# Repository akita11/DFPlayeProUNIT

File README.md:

# DFPlayerProUNIT

DFRobotの音声プレーヤモジュール[DFPlayer Pro](https://www.switch-science.com/products/8005)をGrove端子を接続して制御できるモジュールです。Grove端子からシリアル(UART)通信で音声再生などを制御することができます。（UIFlow(v1)用のブロックも用意する予定）

※DFPlayerProは付属していません

## 使い方（接続方法）

以下のようにスピーカやアンプを接続し、Grove端子からの制御で音声を再生します。また基板上の"PAYE"と"KEY"のシルクが示されている2組の端子は、それぞれDFPlayerProのKEY、PLAY端子に接続されていますので、これらを使って再生を制御することもできます（詳細はDFPlayerProのマニュアルを参照してください）

### アンプ付きスピーカに接続する場合

3.5mmジャック（ステレオ：上部中央）に3.5mmステレオケーブル等でアンプに接続します。

### スピーカを直接接続する場合

本体上部の2つの2.54mmた端子にスピーカを接続します。spkLとspkRがそれぞれお左と右のスピーカです。基板中央部に1.25mmピッチコネクタ(Molex 53047-0210用)をとりつける端子があり、市販の小型スピーカ（M5Stack本体に使われているものなど。AliExpressやTaobaoでも同等品があります）を接続することができます。

### 3.5mmジャックに直接スピーカを接続する方法

3.5mmジャックに直接スピーカを接続することもできます。その場合は、基板裏面のハンダジャンパを以下のように修正してください。

- JP1をカット
- JP2・JP3の中央と△マーク側をカットし、中央と反対側（△マークがない側）をショート

## 使い方（ソフトウエア）

あらかじめ、DFPlayerProをUSB Type-Cケーブルを使ってPCへ接続し、現れるドライブに使用する音声データ（*.mp3等）をコピーしておきます。（このときコピーした順番が、再生時に使用する「曲番号」になります）

### UIFlow(v1)での使い方

「DFPlayerPro.m5b」をダウンロードし、UIFlow(v1)の"Custom"の"Open *.m5b"からこのファイルを指定すると、Init、Play、Volumeの3つのブロックを使用できます。

- DFPlayerPro_Init : 初期化。最初に1回だけ読み出します。"TX"と"RX"には、使用するGroveポート・マイコン本体にあわせて、使用するピン番号を指定します。例えば、M5StackBasicのPortA（本体の赤いコネクタ）の場合は、上図のようにTX=21、RX=22を指定します。M5StackCore2のPortAの場合は、TX=32、RX=33となります。
- DFPlayerPro_Play : numに指定した「曲番号」の音声を再生します。
- DFPlayerPro_Volume : volに指定した音量に設定します。

### その他のソフトウエアでの使い方

Arduino用にはライブラリがあるようなので、そちらを使ってもOKです。
あるいは、DFPlayerProのデータシート等を参考に、制御コマンドを送信して使用してください。

## Author

Junichi Akita (@akita11) / akita@ifdl.jp

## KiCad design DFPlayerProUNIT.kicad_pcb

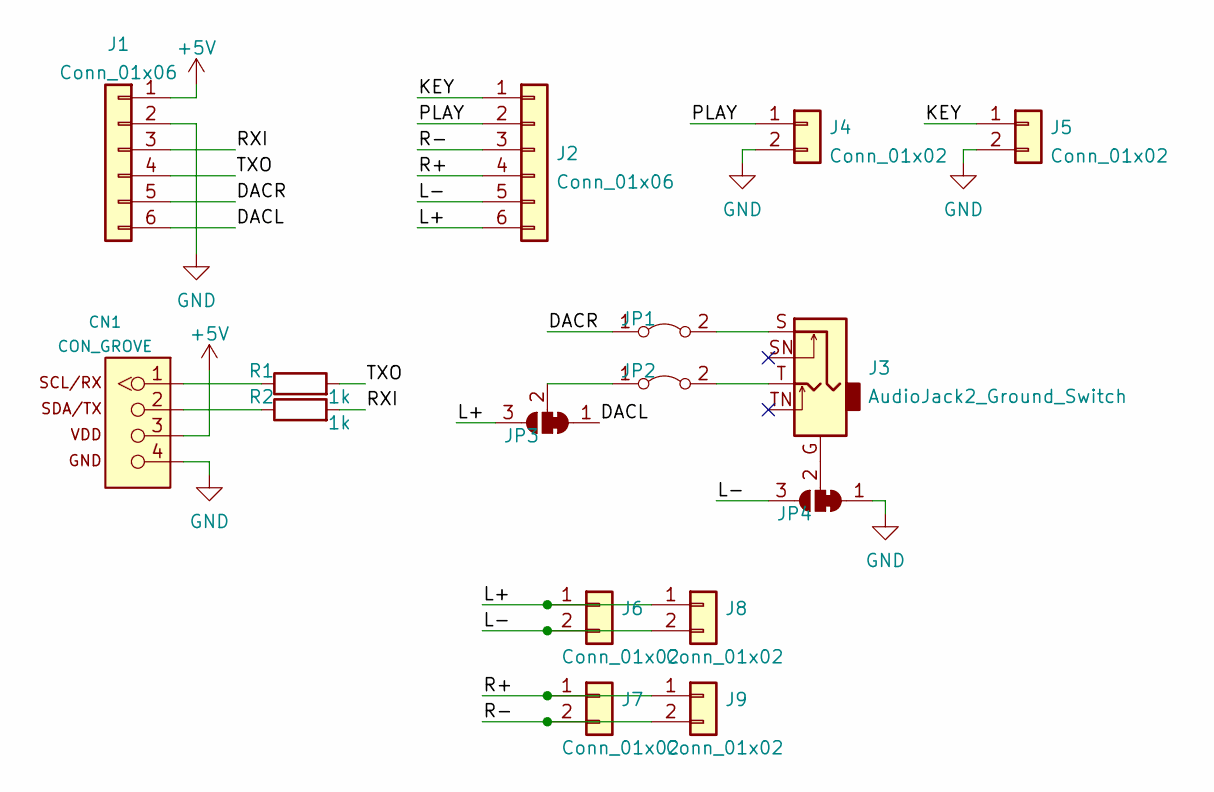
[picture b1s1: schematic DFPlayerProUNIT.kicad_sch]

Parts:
CN1: CON_GROVE; CON_GROVE_H
J1, J2: Conn_01x06; PinSocket_1x06_P2.54mm_Vertical
J3: AudioJack2_Ground_Switch; CON_AJ-1780
J4, J5, J6, J7: Conn_01x02; PinSocket_1x02_P2.54mm_Vertical
J8, J9: Conn_01x02; Molex_PicoBlade_53047-0210_1x02_P1.25mm_Vertical
JP1, JP2: Jumper_2_Bridged; SolderJumper-2_P1.3mm_Bridged2Bar_Pad1.0x1.5mm
JP3, JP4: SolderJumper_3_Bridged12; SolderJumper-3_P1.3mm_Bridged12_Pad1.0x1.5mm
R1, R2: 1k; R_0603_1608Metric

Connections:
+5V: CN1.3, J1.1
/DACL: J1.6, JP3.1 (A)
/DACR: J1.5, JP1.1 (A)
/KEY: J2.1, J5.1
/L+: J2.6, J6.1, J8.1, JP3.3 (B)
/L-: J2.5, J6.2, J8.2, JP4.3 (B)
/PLAY: J2.2, J4.1
/R+: J2.4, J7.1, J9.1
/R-: J2.3, J7.2, J9.2
/RXI: J1.3, R2.2
/TXO: J1.4, R1.2
GND: CN1.4, J1.2, J4.2, J5.2, JP4.1 (A)
unnamed: CN1.1, R1.1
unnamed: CN1.2, R2.1
unnamed: J3.S, JP1.2 (B)
unnamed: J3.T, JP2.2 (B)
unnamed: JP2.1 (A), JP3.2 (C)
unnamed: J3.G, JP4.2 (C)

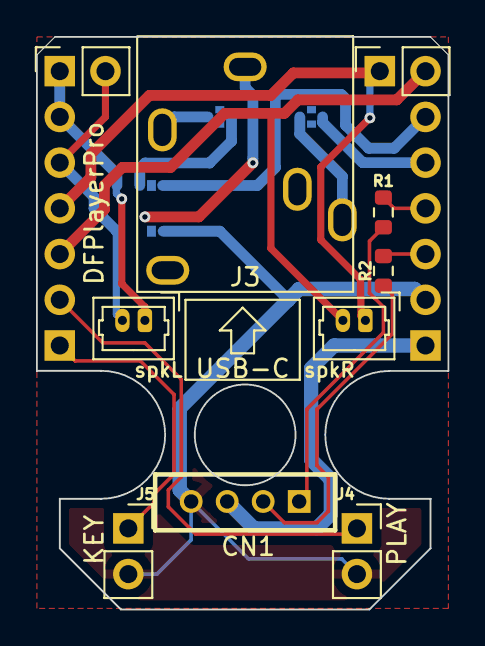
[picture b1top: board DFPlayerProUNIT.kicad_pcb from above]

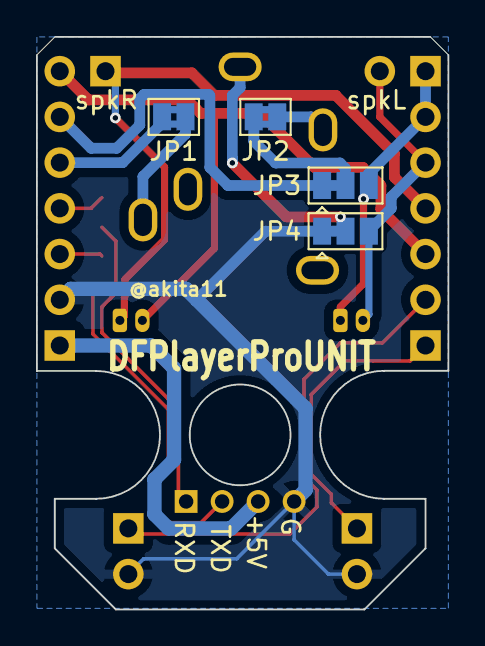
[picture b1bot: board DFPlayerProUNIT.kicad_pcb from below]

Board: 2 copper layers, 22.9 x 31.8 mm, 16 parts (4 on the bottom side), 18 nets.

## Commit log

2025-01-02 add photo
2025-01-02 typo fix
